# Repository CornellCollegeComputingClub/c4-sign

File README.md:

# C4 Sign
funny sign go brrrrrrrr

The C4 Sign is an LED sign that students can write programs for to display at our events on campus!
Programs can be written in either Java or Python.
It features a 32x32 color LED display for graphics and a 16x2 character LCD screen for text.

If you are interested in writing a display program for it, please make a fork of this repository.
Get in touch with us if you have any questions or want advice for how to write your program!

The LED Sign channel of our discord server is a great place to get advice both from club executives and from other students.
Feel free to make whatever you like for the sign, this is a chance to use your programming skills to channel your creativity and self-expression!

## Tutorial

Check [the tutorial](./docs/tutorial.md) to learn how you can begin writing your own sign programs.

## Program Examples
You can watch each display program [here](./docs/screen_tasks.md).
If you want to see how each task works, the programs can be found in `/c4_sign/screen_tasks` and `/c4_sign/java_c4sign/src/main/java/com/cornellcollegecomputingclub/c4sign_tasks`.

## Documentation
Our documentation is currently incomplete, but much of the screen's workings can be found in the `/docs/` directory.
See the [documentation home page](./docs/index.md).

## Simulator

The simulator is a simple program that simulates the sign.
It allows you to write programs for the sign without physical access!

It shows you a visualization of the 32 by 32 pixel matrix, and the attached 16x2 character LCD screen.
You can use the dropdown menu at the bottom to choose a task to run, then press 'send' to run it.

You can use the simulator to test out your program without needing to be near the sign all the time!
Whenever you make changes to your program, visualizing them is as simple as running the above command and selecting it in the simulator

## Wishlist
The following is a list of programs that could be neat to have on our sign!
If you are unsure what to make, you can use the list below as inspiration.

* [A digital 'rain' effect, like from The Matrix](https://www.youtube.com/watch?v=MUVo20q6tx8)
* [Something like boids!](https://www.youtube.com/watch?v=bqtqltqcQhw)
* [Something like the bouncing DVD logo!](https://www.youtube.com/watch?v=QOtuX0jL85Y)
* [Something like Conway's game of life!](https://www.youtube.com/watch?v=C2vgICfQawE)
* Simulating a classic video game, like [Spacewar](https://www.youtube.com/watch?v=1EWQYAfuMYw&t=729), [Tetris](https://www.youtube.com/watch?v=O0gAgQQHFcQ), [Breakout](https://www.youtube.com/watch?v=NOGO49j5gCE), or [Pong](https://www.youtube.com/watch?v=fiShX2pTz9A)
* Simulated fireworks!
* Something that displays the Message of the Day! (Found in `/c4_sign/consts.py`)
* Something to celebrate the season or something you like!

If you want to make something, but are struggling with ideas, feel free to reach out to us or ask in our Discord.

# Installation

In order to make a program that runs on the sign, you will have to locally install the sign software and simulator so that you can test your program.

Here's how you can install the C4 Sign software:

1. Make sure you have [Python](https://www.python.org/downloads/) and [Git](https://git-scm.com/install/) installed. Python 3.9 or above should be good. *If you want to write your program with Java, which is recommended for graphics-intense tasks, make sure to also install [Maven](https://maven.apache.org/).*
2. Sign into Github and make a fork of this repository.
3. Navigate to the folder where you would like to download the software, and clone your fork of our git repository!
`git clone https://github.com/{Your username here}/c4-sign`
4. Enter the `c4-sign` repository by typing `cd c4-sign`.
5. **Optional:** If you want to, you can create a virtual environment for this project. If you don't know what a virtual environment is, you can skip this step. If you want to make one, run `python3 -m venv ./venv` and then activate the virtual environment in whichever way you typically do that with your operating system.
6. Run `python3 -m pip install -e '.[simulator]'`. This will install the simulator software on your computer.

Congrats! You can now run the simulator in **python-only** mode. To do so, run:
`python3 -m c4_sign --simulator --disable-java` and a new web browser window will appear with the simulator! It may take a while for that to happen as it will download certain resources first.

If you want to work with Java, there are a few more steps. Again, make sure [Maven](https://maven.apache.org/) is installed!
  
7. Run `python3 tools/setup_java_project.py`. This will make sure the necessary Java and Python dependencies are available.  
8. Run `python3 tools/compile_java_project.py`. This will compile the Java project correctly for the sign software to use it. **You must run this command every time you want to test changes to a Java file.**

Nice! Now you can run the simulator in **python and java mode**. To do so, run:
`python3 -m c4_sign --simulator`. The Java and the Python tasks should now be available!

Problems?

Please email us or ask for help in the `#led-sign` channel of our discord server!

## Hardware
You can find CAD models of the C4 sign in the `./hardware` directory.
You can also view more information about the physical design including the original Onshape documents [here](./hardware/hardware.md).

## Updates

The C4 Sign automatically pulls from this repository under the following conditions:
- Every 24 hours (shortly after midnight)
- When the script is first launched (after like a reboot)

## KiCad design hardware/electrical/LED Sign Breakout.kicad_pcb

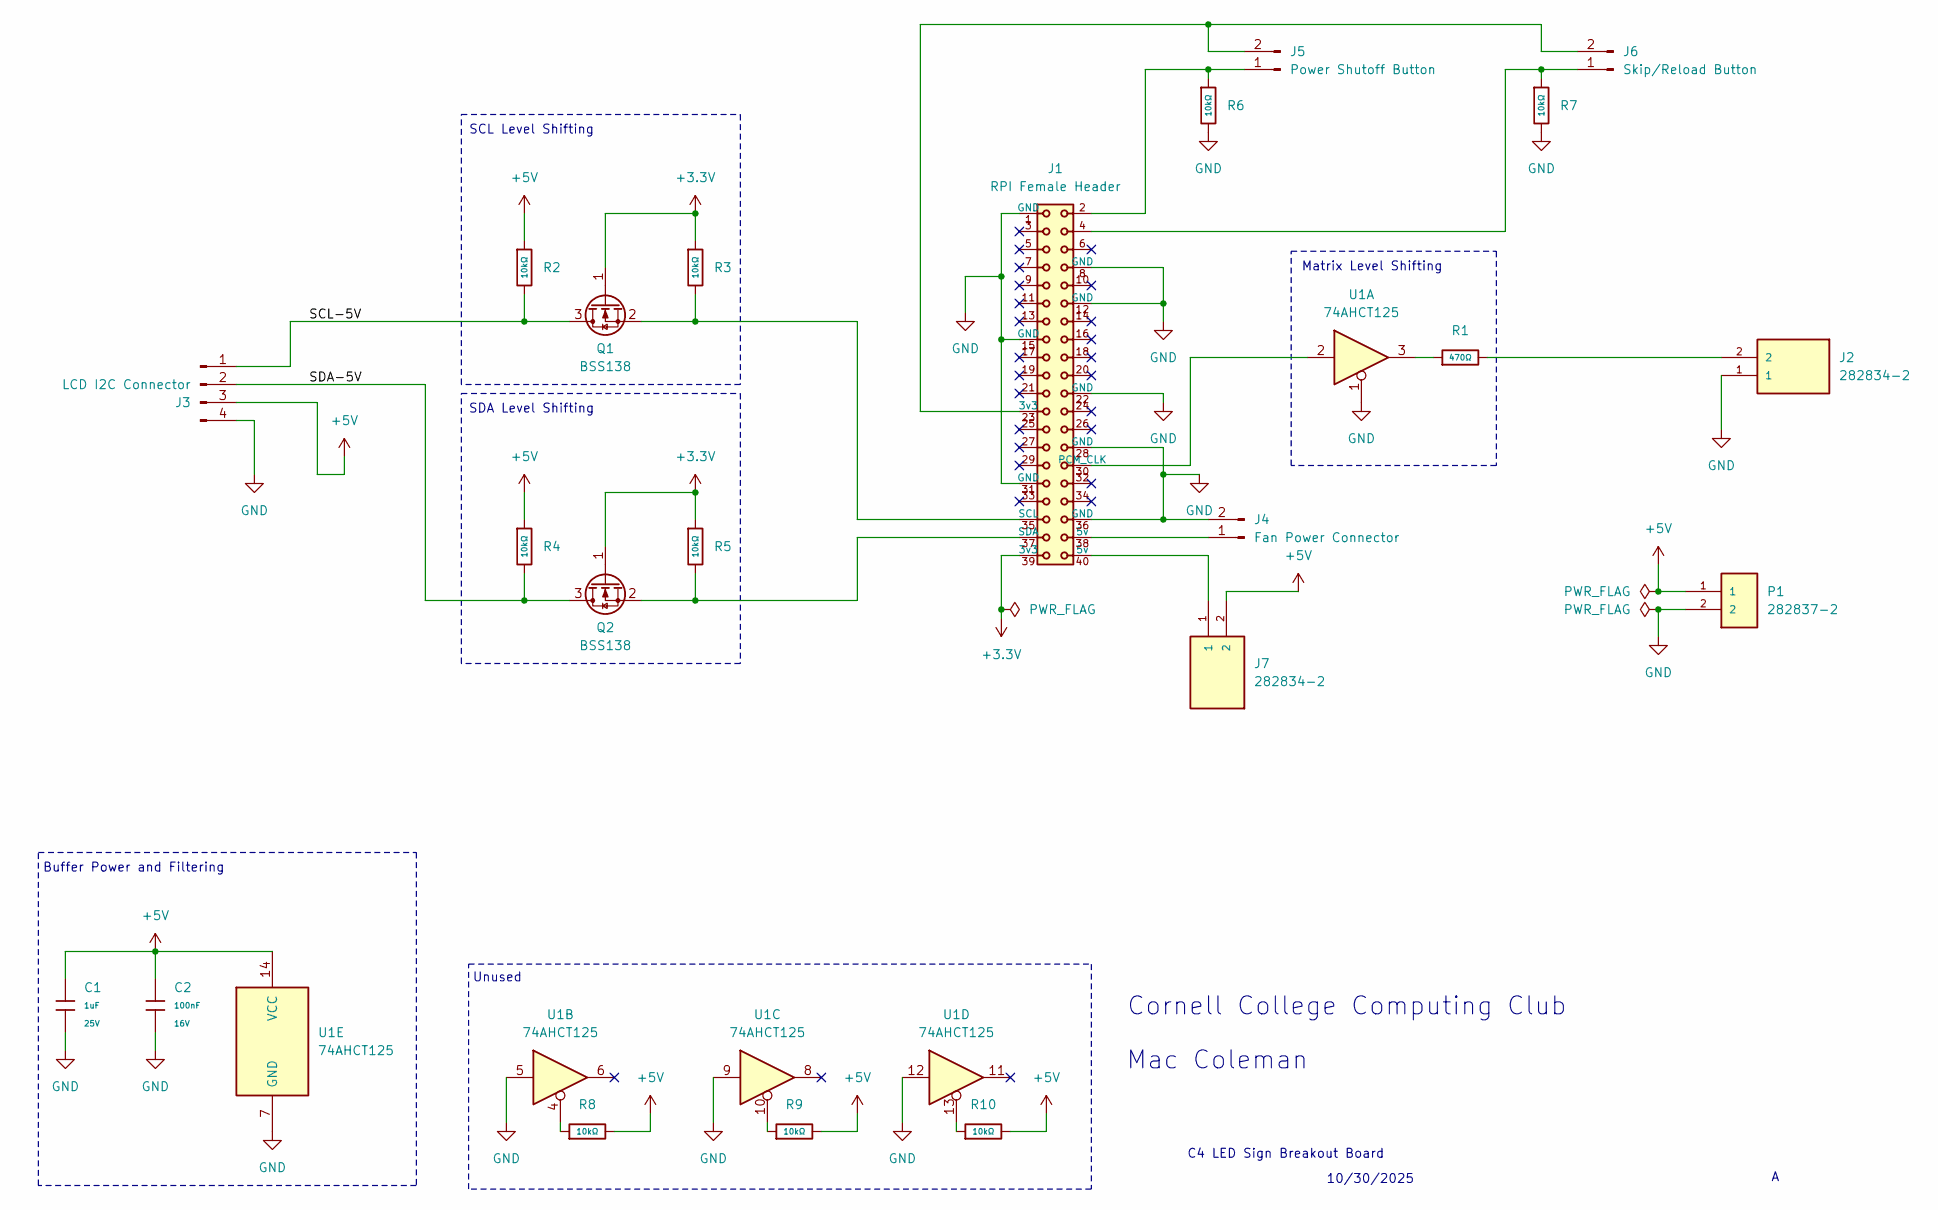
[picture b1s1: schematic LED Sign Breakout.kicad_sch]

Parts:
C1: 1uF; C_0402; Voltage Rated 25V; Tolerance ±10%; Part CL05A105KA5NQNC; LCSC C52923
C2: 100nF; C_0402; Voltage Rated 16V; Tolerance ±10%; Part CL05B104KO5NNNC; LCSC C1525
J1: RPI Female Header; 61304021821
J2, J7: 282834-2; TE_282834-2; PARTREV D
J3: LCD I2C Connector; PinHeader_1x04_P2.54mm_Horizontal_I2C
J4: Fan Power Connector; PinHeader_1x02_P2.54mm_Horizontal_Fan
J5: Power Shutoff Button; PinHeader_1x02_P2.54mm_Horizontal_Pinless
J6: Skip/Reload Button; PinHeader_1x02_P2.54mm_Horizontal_Pinless
P1: 282837-2; TE_282837-2; PARTREV G3
Q1, Q2: BSS138; SOT-23; LCSC C8490
R1: 470Ω; R_0402; Overload Voltage (Max) 50V; Tolerance ±1%; Part 0402WGF4700TCE; LCSC C25117
R2, R3, R4, R5, R6, R7, R8, R9, R10: 10kΩ; R_0402; Overload Voltage (Max) 50V; Tolerance ±1%; Part 0402WGF1002TCE; LCSC C25744
U1: 74AHCT125; SOIC-14_3.9x8.7mm_P1.27mm; LCSC C155176

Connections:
+3.3V: J1.39 (3v3), Q1.1 (G), Q2.1 (G), R3.1, R5.1
+5V: C1.1, C2.1, J3.3, J7.2, P1.1, R2.1, R4.1, R8.2, R9.2, R10.2, U1.14 (VCC)
/SCL-5V: J3.1, Q1.3 (D), R2.2
/SDA-5V: J3.2, Q2.3 (D), R4.2
GND: C1.2, C2.2, J1.1 (GND), J1.8 (GND), J1.12 (GND), J1.15 (GND), J1.22 (GND), J1.28 (GND), J1.31 (GND), J1.36 (GND), J2.1, J3.4, J4.2, P1.2, R6.2, R7.2, U1.1, U1.5, U1.7 (GND), U1.9, U1.12
unnamed: J1.40 (5v), J7.1
unnamed: J1.30 (PCM_CLK), U1.2
unnamed: J1.35 (SCL), Q1.2 (S), R3.2
unnamed: J1.37 (SDA), Q2.2 (S), R5.2
unnamed: J2.2, R1.2
unnamed: J1.38 (5v), J4.1
unnamed: J1.2, J5.1, R6.1
unnamed: J1.23 (3v3), J5.2, J6.2
unnamed: J1.4, J6.1, R7.1
unnamed: R1.1, U1.3
unnamed: R8.1, U1.4
unnamed: R9.1, U1.10
unnamed: R10.1, U1.13

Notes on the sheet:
Mac Coleman
SDA Level Shifting
Matrix Level Shifting
Buffer Power and Filtering
Unused
SCL Level Shifting
C4 LED Sign Breakout Board
10/30/2025
Cornell College Computing Club

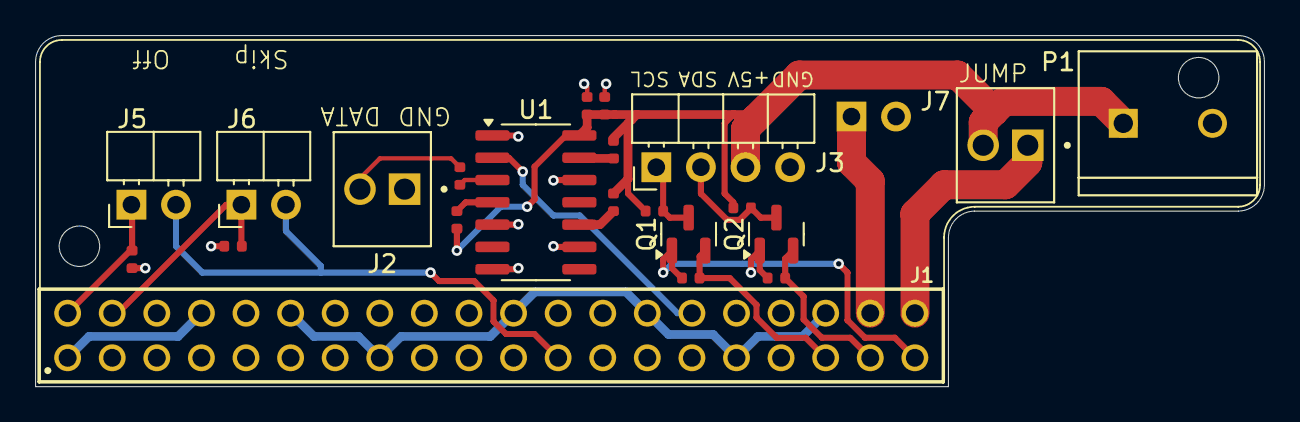
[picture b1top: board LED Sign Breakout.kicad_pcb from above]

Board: 2 copper layers, 70.0 x 20.0 mm, 23 parts (1 on the bottom side), 18 nets.

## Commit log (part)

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2024-01-31 inital fork from krnl-sign, start pruning
2024-01-31 Remove RGBMatrix imports
2024-01-31 Update repository URLs
    this thing can actually be installed now!
    well not really. it will error out almost immediately. but it's a start!
2024-02-11 add lib folder
2024-02-12 add canvas, code improvements
2024-02-12 Added basic graphics headers
2024-02-12 Added debug method to canvas objects
2024-02-12 Bresenham's line algorithm implemented
2024-02-12 Implemented rectangle stroking and filling
2024-02-12 Basic, lazy implementation of image drawing
2024-02-12 Added ellipse methods
2024-02-12 Added transparency calculations to image drawing routine
2024-02-13 Changed image drawing logic to cut overflow
2024-02-16 Add I2C library and LCD driver code
2024-02-19 Changed test to random colors, began to make 'simulator' use alt buffer
2024-02-19 Completed alternate buffer transformation
2024-02-19 Show/hide cursor in simulation mode
2024-02-20 Demo task color changes, corrected lcd methods in examples
2024-02-23 Add LCD functionality to MatrixScreen and update SimulatorScreen
2024-02-24 remove typehints for now
    also: add smbus & fix some imports
2024-02-24 start messing with physical sign
2024-02-24 fix typings, format code better
2024-02-24 add more details to readme
2024-02-24 remove profiling, fix typing
2024-02-24 make lcd display title and author by default
2024-02-24 websocket server start
2024-02-24 Add canvas and LCD display to index.html
2024-02-24 expose some debug info!
2024-02-24 Update screen.py to handle null current_task values
2024-02-24 cache functionality!!
2024-02-24 actually make that importable
2024-02-24 fix error display
2024-02-25 Renamed demo class, added rainbow wave
2024-02-25 bad apple subtitles! lcd shows on simulator!
2024-02-25 lint, add docs and resize to asset collection
2024-02-25 have simulator run as close to 24fps as it can
2024-02-25 Added pong task
2024-02-25 Added type hint for alpha in fill_rect
2024-02-25 Added rainbow trails to paddles in pong task
2024-02-25 Added mandelbrot set task
2024-02-25 add snazzy border to screens
2024-02-25 Continuous Coloring for Mandelbrot set
2024-02-25 Add burning ship set
2024-02-25 Added Julia Sets
2024-02-25 add sorting algos, util functions
2024-02-26 add the worst (best?) one yet-
2024-02-26 add autoflake to justfile
2024-02-26 run linters
2024-02-27 Update install.sh script
2024-02-27 Add loading message to MatrixScreen display
2024-02-27 make lcd noop temporarily
2024-02-27 add tmp profiling
2024-02-28 Documentation Started
2024-02-28 revert testing commits, add new flags
    new flags: --gif and --profile! pretty self-explanatory i feel
2024-02-29 add some documentation on internals and some resources
2024-03-01 Reduced max iterations of burning ship set
2024-03-01 Filled out more of graphics library documentation
2024-03-01 Added anchors to table of contents for graphics lib docs
2024-03-01 add canvas example image to documentation
2024-03-01 add google drive support
2024-03-02 Corrected my typos in graphics lib docs
2024-03-02 Untested addressing code
2024-03-02 add images to graphics documentation
2024-03-02 add loading progress to startup, purge cache flag, better ffmpeg
2024-03-02 make color ints be 0x(aa)rrggbb, adjust documentation
    because if its 0xrrggbbaa, and red is 0, RRGGBBAA will be parsed as __RRGGBB, which isn't ideal.
2024-03-02 implement scanline polygon fill algorithm
2024-03-02 re-enable rick roll
2024-03-02 fix merge sort, fix wording on things
2024-03-02 add sorting colors, slow it down a bit
2024-03-02 Added comments on font sizes.
2024-03-02 Made alpha demo clearer
2024-03-02 a lot of improvements~!
    gif mode now generates documentation
    weather now doesnt rely on a function, instead uses the power of hashmaps
    move rick & bad apple subtitles to google drive
    made override a dropdown in simulator
2024-03-02 Added documentation for assets functions
2024-03-02 Added comment on our google drive
2024-03-02 fix even more typos
2024-03-04 add gif of screen tasks
2024-03-06 fix some bugs and typos!
    - draw centered text now no longer produces visual artifacts
    - bad apple & rick roll now obey time properly
    - tutorial documentation typos eliminated
2024-03-22 Reordered loading_screen in MatrixScreen
2024-03-22 optimize the heck out of neopixels
2024-03-22 fix typo
    i cannot type!
2024-03-22 Fix pixel data type conversion issue (and typos)
2024-03-22 fix things
2024-03-22 Update DEV_MODE flag and screen_active function so we don't turn off at midnight
2024-03-22 make fixup go everywhere, one of these days itll work
2024-03-22 Fix pixel data type conversion issues, hopefully
2024-03-22 fix adafruit code
2024-03-22 Change profiler settings
2024-03-22 Testing numba
2024-03-22 Revert "Testing numba"
    This reverts commit bf392a9b47abcd2c7ed9ee6e4a5e333127efee50.
2024-03-25 Revert "hopefully speedup draw_image"
    This reverts commit 0abeeb979c2df867e660be579238e5564392c1a9.
2024-03-25 Add Addressing (#1)
2024-03-25 Add a bunch of stuff!
    Refactor new NeoPixel lib
    Disable CoordinateTest and DemoTask
    Fix typo in tutorial
    Delete example code (since it really wasn't an example for the sign.)
2024-03-25 convert gifs to webp
    saves about 50% per task! also fixes frame rate, which is lovely.
2024-03-25 add cache functionality to screen task
    cursed. oh so cursed. i need to take a shower after this one
2024-03-25 Naive drawing thread implementation
2024-03-25 Explosion Message of the day task, MOTD text in consts.py
2024-03-25 Forgot to return true from Prepare
2024-03-25 fix type hints
2024-03-26 disable burning ship, run formatter, add gif for explosion
    also make gif mode delete anything that is disabled instead of waiting
    for a purge run
    # Conflicts:
    # c4_sign/screen_tasks/burning_ship.py
2024-03-26 disable optim debug text
2024-03-29 documentation tweaks
2024-04-20 Update MOTD text
2024-04-20 Change brightness
2024-04-22 Update readme, add to docs index
2024-04-22 Add tutorial link to readme
2024-04-25 add various optimizations! (#2)
2024-04-25 add percolate task
    right now the color is white, not sure if im sold on that tbh
2024-08-09 stop adding new cells when complete
2024-08-09 hopefully add pr image generation
2024-08-09 fix install because i am foolish
2024-08-09 fix pr fonts
2024-08-09 update pr comment version
    i swear im going insane
2024-11-14 ensure that the physical sign uses a venv
2024-11-14 dont actually import the emulator on every run
2024-11-14 migrate to yt-dlp over cobalt
    you shall be missed, cobalt
2024-11-15 actually finish the tutorial
    ...mostly
2024-11-16 Added Stick_Fight Subprogram
2024-11-16 Added Stick_Fight Subprogram (#4)
2024-11-16 add visuals to loading
2024-11-16 remove sleep from sorting_algos
    now, it just passes every other frame instead of sleeping for .05
    (making it now run at 12 fps instead of 16, but its cleaner)
2024-11-16 refactor logging level from debug to trace in NeoPixel class
2024-11-16 refactor logging level from debug to trace in matrixscreen
2024-11-16 fix weather codes
2024-11-16 shuffle screen tasks with a fixed random seed for consistency
2024-11-16 delete pr preview for now
    later problem tbh, need to recreate comment-pr-with-image
2024-11-16 try to add more thread safety to neopixel
    maybe this is it?
2024-11-16 test using rpi_ws281x
2024-11-16 use color from rpi_ws281
2024-11-16 use int for pin over board lib
2024-11-16 add uptime task
2024-11-17 im a fool
2024-11-17 add clocks to uptime
2024-11-17 add fps to uptime (and disable it)
2024-11-17 Switch to rpi_ws281x (#5)
    also adds uptime task (currently disabled)
2024-11-18 fix typo in algorithms
2024-11-18 update percolate and algos colors
2024-11-19 change name on license
    ...yeah...
2024-11-20 Add debug mode with system stats and logging functionality
2024-11-20 First test of Java building with Maven
    Adds Py4j as a dependency.
2024-11-20 Added commons-lang3 as a java dependency
2024-11-20 Added Constants.java
2024-11-20 Added prepare and teardown methods to java base class
2024-11-20 Added a random java task
2024-11-20 Fixed name of task!
2024-11-20 Added --no-upload flag
    Skips uploading of histogram files
2024-11-20 Changed RainbowWaveJava to more accurately reflect the Python RainbowWave.
2024-11-20 Added py4j to setup.py
    This adds py4j.jar to your python installations! Somewhere around
    share/py4j/py4j0.x.x.x.jar...
2024-11-21 Added a basic setup script to move py4j to the maven repository!
2024-11-21 Added new error messages for setup failure
2024-11-21 pretty up simulator a little
2024-11-21 update layout to center elements vertically in the simulator
2024-11-21 refactor screen into a class
2024-11-22 Added command to start java server
2024-11-22 Automatically start and wait for gateway server, add --disable-java flag
2024-11-22 Added maven to install script
2024-11-22 Added setup and compile steps to install.sh
2024-11-22 Translated compile_java_project.sh to python
2024-11-22 Translated start_java_server.sh to python
2024-11-23 Translated setup_java_project.sh to python
2024-11-23 Make python main program run python java server, change simulator task naming and overriding to be title-based
    Maybe we should have some sort of canonical name for each task?
2024-11-23 Changed error message to reflect new python script
2024-11-25 Used Py4J "Launch Gateway" method instead of custom subprocess.Popen command. Should be more reliable...
2024-11-25 Remove tools/start_java_server.py
    The user should never need to start the java server on their own...
2024-12-01 fix paths
2024-12-02 Revert "Merge branch 'java' of https://github.com/CornellCollegeComputingClub/c4-sign into java"
    This reverts commit 77b6dcfc4a44e6a7e9add92f66e6ef155fcb363a, reversing
    changes made to 72ccaf031dfb82a23dd0e384d58189b1d8391bcc.
2024-12-02 Returned Status from Java
2024-12-02 add really horrible memory stress test
2024-12-02 add histogram, profile support
2025-02-12 Bump Py4J version, update Java setup + compilation scripts
2025-02-12 Added rainbow colors to Lissajous to demonstrate Java BufferedImage uses
2025-02-13 Fixed operating system compatibility in build scripts
2025-02-13 Fixed classpath to add commons-lang3 to py4j server
2025-02-13 Fixed usage of JavaTaskBase's getLcdText method in python JavaTask class
2025-02-14 Fixed JavaTaskBase getLcdText default implementation to match Python get_lcd_text default implementation
2025-02-17 Forgot to return true
2025-02-18 Attempt to remove Neopixel class
2025-02-18 Forgot to save file :(
2025-02-18 Fix types before turning to Color
2025-02-18 fixed lambda definition
2025-02-18 Deleted Neopixel class
2025-02-18 Added sleep implementation to MatrixScreen to match SimulatorScreen
2025-02-18 Disable TimingTest
2025-02-18 Disable JVMStressTest. I still need to implement ignored tasks in Java
2025-02-19 Fix colors in java task
2025-02-19 Add option to specify starting task for faster testing
2025-02-19 Attempt gamma correction for sign
2025-02-19 Limit brightness during gamma correction
2025-02-19 Fix broken condition in init_screen
2025-02-28 New Double Pendulum task to test basic Verlet integration physics
2025-02-28 Fixed bug causing screen to not be updated before override with --starting-task
2025-09-01 Changing tasks that use complex numbers to use the python complex type
    i didn't know it existed
2025-09-03 Fixed teardown methods for Java Tasks
2025-09-03 Added new "Cornell Gears" task
    Spinning gears with Cornell "C"
2026-02-10 Finally updated the --gif option to use canonical names instead of class names
2026-02-10 Update main sign image
2026-02-10 Updated README to have more thorough information about Java tasks
2026-02-10 Updated to use canonical names where possible
2026-02-11 Updated matrix to use perf_counter_ns instead of arrow to reduce jitter
2026-02-11 Forgot to use same units for delay
